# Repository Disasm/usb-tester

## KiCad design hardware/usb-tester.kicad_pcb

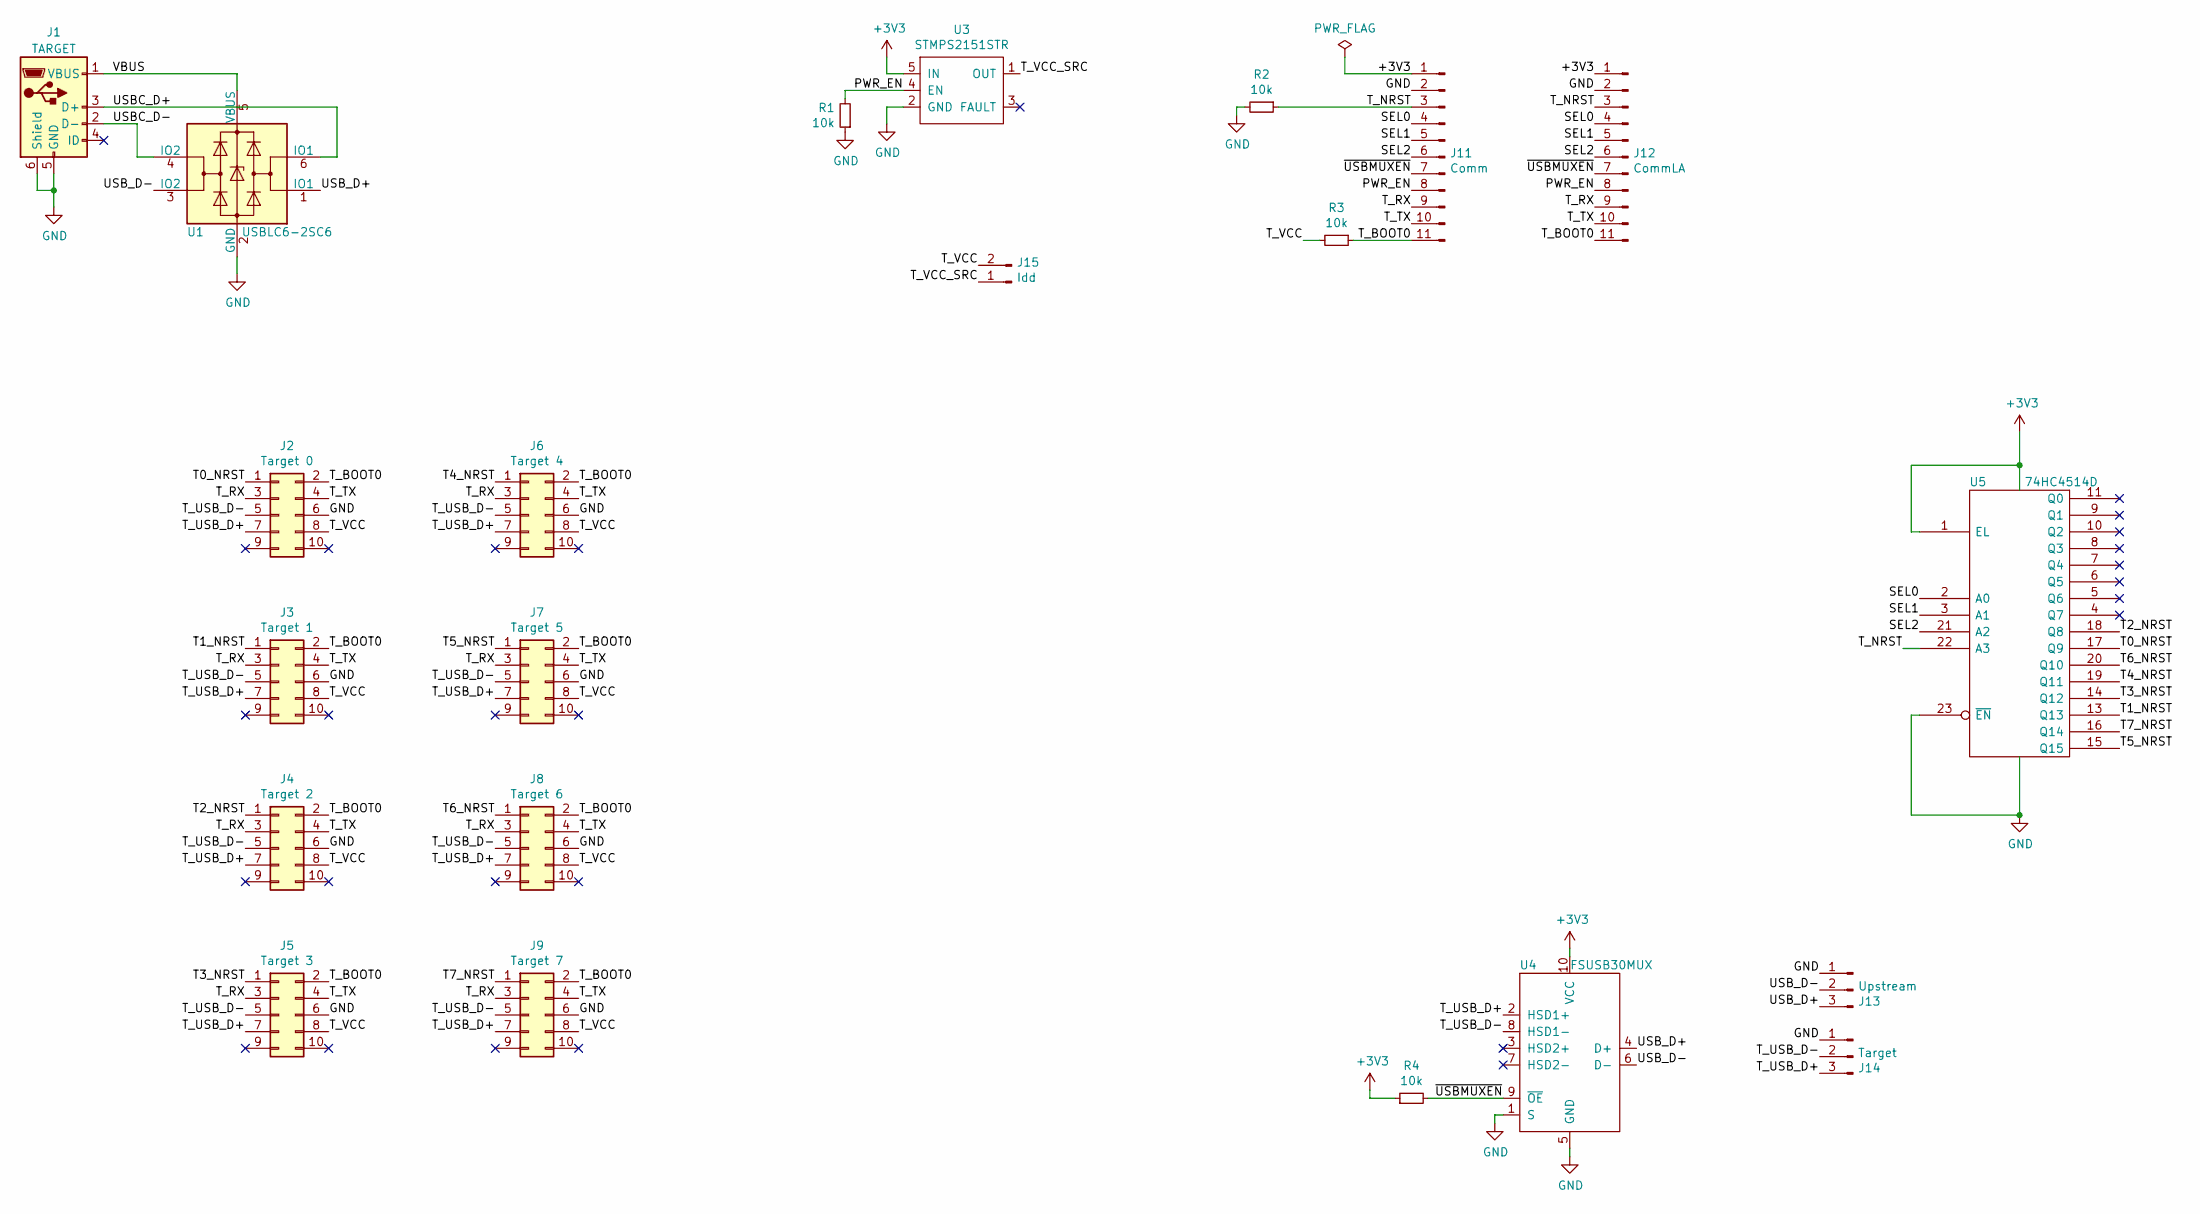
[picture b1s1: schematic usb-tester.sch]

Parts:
J1: TARGET; USB_Micro-B_Molex-105017-0001
J2: Target 0; PinSocket_2x05_P2.54mm_Vertical_Reversed
J3: Target 1; PinSocket_2x05_P2.54mm_Vertical_Reversed
J4: Target 2; PinSocket_2x05_P2.54mm_Vertical_Reversed
J5: Target 3; PinSocket_2x05_P2.54mm_Vertical_Reversed
J6: Target 4; PinSocket_2x05_P2.54mm_Vertical_Reversed
J7: Target 5; PinSocket_2x05_P2.54mm_Vertical_Reversed
J8: Target 6; PinSocket_2x05_P2.54mm_Vertical_Reversed
J9: Target 7; PinSocket_2x05_P2.54mm_Vertical_Reversed
J11: Comm; PinHeader_1x11_P2.54mm_Vertical
J12: CommLA; PinHeader_1x11_P2.54mm_Vertical
J13: Upstream; PinHeader_1x03_P2.54mm_Vertical
J14: Target; PinHeader_1x03_P2.54mm_Vertical
J15: Idd; PinHeader_1x02_P2.54mm_Vertical
R1, R2, R3, R4: 10k; R_1206_3216Metric_Pad1.42x1.75mm_HandSolder
U1: USBLC6-2SC6; SOT-23-6
U3: STMPS2151STR; SOT-23-5
U4: FSUSB30MUX; MSOP-10_3x3mm_P0.5mm
U5: 74HC4514D; SOIC-24W_7.5x15.4mm_P1.27mm

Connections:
+3V3: J11.1, J12.1, R4.1, U3.5 (IN), U4.10 (VCC), U5.1 (EL), U5.24 (Vdd)
/PWR_EN: J11.8, J12.8, R1.2, U3.4 (EN)
/SEL0: J11.4, J12.4, U5.2 (A0)
/SEL1: J11.5, J12.5, U5.3 (A1)
/SEL2: J11.6, J12.6, U5.21 (A2)
/T0_NRST: J2.1, U5.17 (Q9)
/T1_NRST: J3.1, U5.13 (Q13)
/T2_NRST: J4.1, U5.18 (Q8)
/T3_NRST: J5.1, U5.14 (Q12)
/T4_NRST: J6.1, U5.19 (Q11)
/T5_NRST: J7.1, U5.15 (Q15)
/T6_NRST: J8.1, U5.20 (Q10)
/T7_NRST: J9.1, U5.16 (Q14)
/T_BOOT0: J2.2, J3.2, J4.2, J5.2, J6.2, J7.2, J8.2, J9.2, J11.11, J12.11, R3.1
/T_NRST: J11.3, J12.3, R2.1, U5.22 (A3)
/T_RX: J2.3, J3.3, J4.3, J5.3, J6.3, J7.3, J8.3, J9.3, J11.9, J12.9
/T_TX: J2.4, J3.4, J4.4, J5.4, J6.4, J7.4, J8.4, J9.4, J11.10, J12.10
/T_USB_D+: J2.7, J3.7, J4.7, J5.7, J6.7, J7.7, J8.7, J9.7, J14.3, U4.2 (HSD1+)
/T_USB_D-: J2.5, J3.5, J4.5, J5.5, J6.5, J7.5, J8.5, J9.5, J14.2, U4.8 (HSD1-)
/T_VCC: J2.8, J3.8, J4.8, J5.8, J6.8, J7.8, J8.8, J9.8, J15.2, R3.2
/T_VCC_SRC: J15.1, U3.1 (OUT)
/USBC_D+: J1.3 (D+), U1.6 (IO1)
/USBC_D-: J1.2 (D-), U1.4 (IO2)
/USB_D+: J13.3, U1.1 (IO1), U4.4 (D+)
/USB_D-: J13.2, U1.3 (IO2), U4.6 (D-)
/VBUS: J1.1 (VBUS), U1.5 (VBUS)
/~USBMUXEN: J11.7, J12.7, R4.2, U4.9 (~OE)
GND: J1.5 (GND), J1.6 (Shield), J2.6, J3.6, J4.6, J5.6, J6.6, J7.6, J8.6, J9.6, J11.2, J12.2, J13.1, J14.1, R1.1, R2.2, U1.2 (GND), U3.2 (GND), U4.1 (S), U4.5 (GND), U5.12 (Vss), U5.23 (~EN)

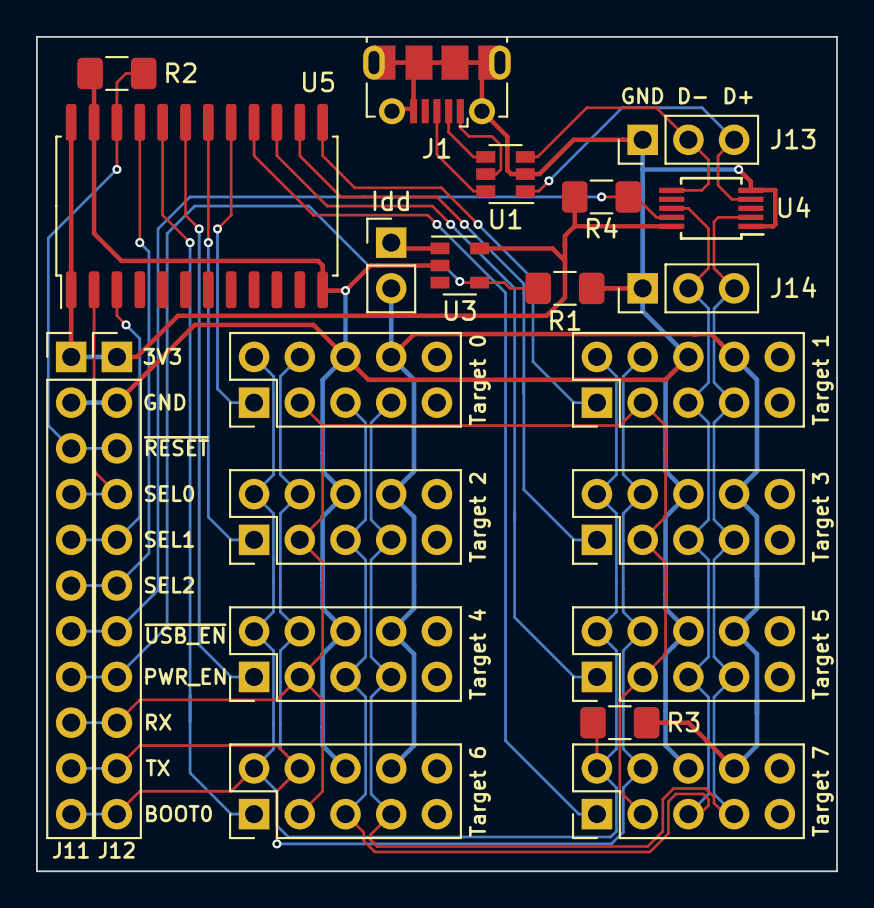
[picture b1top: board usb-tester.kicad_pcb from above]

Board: 2 copper layers, 44.5 x 46.4 mm, 22 parts (0 on the bottom side), 28 nets.

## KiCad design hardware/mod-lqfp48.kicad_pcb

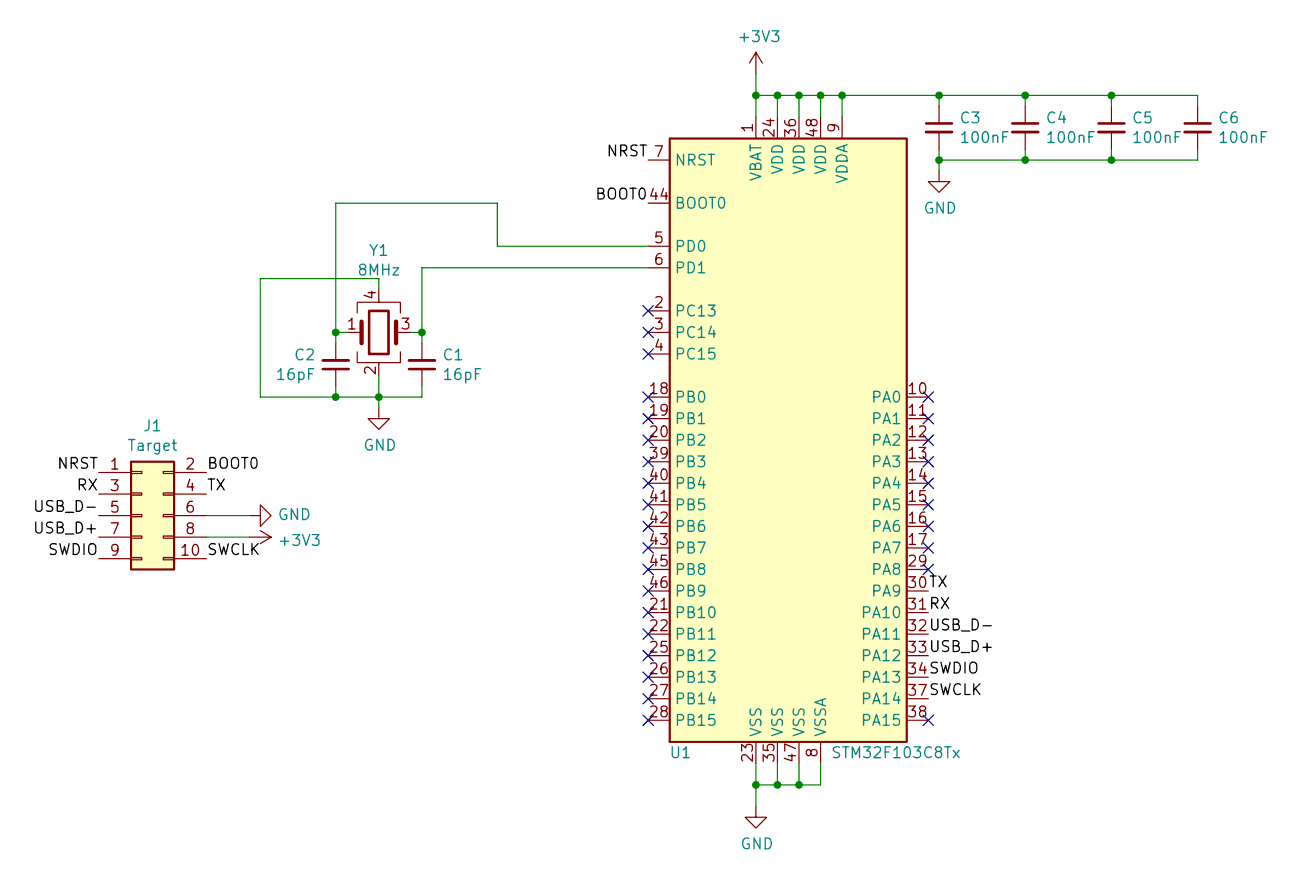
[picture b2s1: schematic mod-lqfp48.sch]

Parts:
C1, C2: 16pF; C_0805_2012Metric_Pad1.15x1.40mm_HandSolder
C3, C4, C5, C6: 100nF; C_0805_2012Metric_Pad1.15x1.40mm_HandSolder
J1: Target; BH-10-Edge
U1: STM32F103C8Tx; LQFP-48_7x7mm_P0.5mm
Y1: 8MHz; Crystal_SMD_5032-4Pin_5.0x3.2mm

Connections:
+3V3: C3.1, C4.1, C5.1, C6.1, J1.8, U1.1 (VBAT), U1.9 (VDDA), U1.24 (VDD), U1.36 (VDD), U1.48 (VDD)
/BOOT0: J1.2, U1.44 (BOOT0)
/NRST: J1.1, U1.7 (NRST)
/RX: J1.3, U1.31 (PA10)
/SWCLK: J1.10, U1.37 (PA14)
/SWDIO: J1.9, U1.34 (PA13)
/TX: J1.4, U1.30 (PA9)
/USB_D+: J1.7, U1.33 (PA12)
/USB_D-: J1.5, U1.32 (PA11)
GND: C1.1, C2.1, C3.2, C4.2, C5.2, C6.2, J1.6, U1.8 (VSSA), U1.23 (VSS), U1.35 (VSS), U1.47 (VSS), Y1.2, Y1.4
unnamed: C1.2, U1.6 (PD1), Y1.3
unnamed: C2.2, U1.5 (PD0), Y1.1

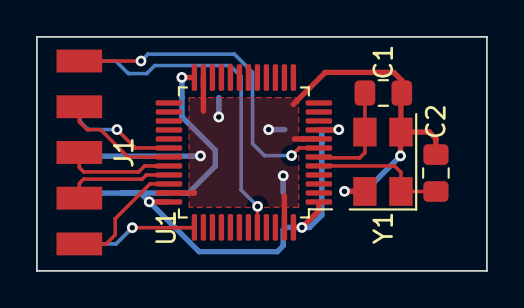
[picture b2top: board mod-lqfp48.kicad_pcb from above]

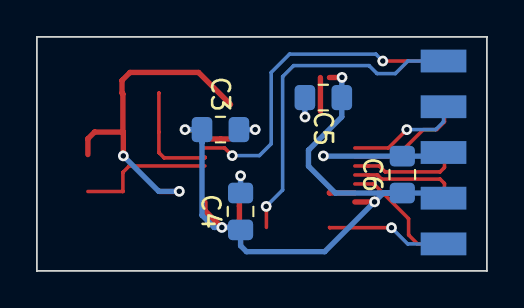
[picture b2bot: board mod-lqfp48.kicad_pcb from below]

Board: 2 copper layers, 25.0 x 13.0 mm, 9 parts (4 on the bottom side), 12 nets.

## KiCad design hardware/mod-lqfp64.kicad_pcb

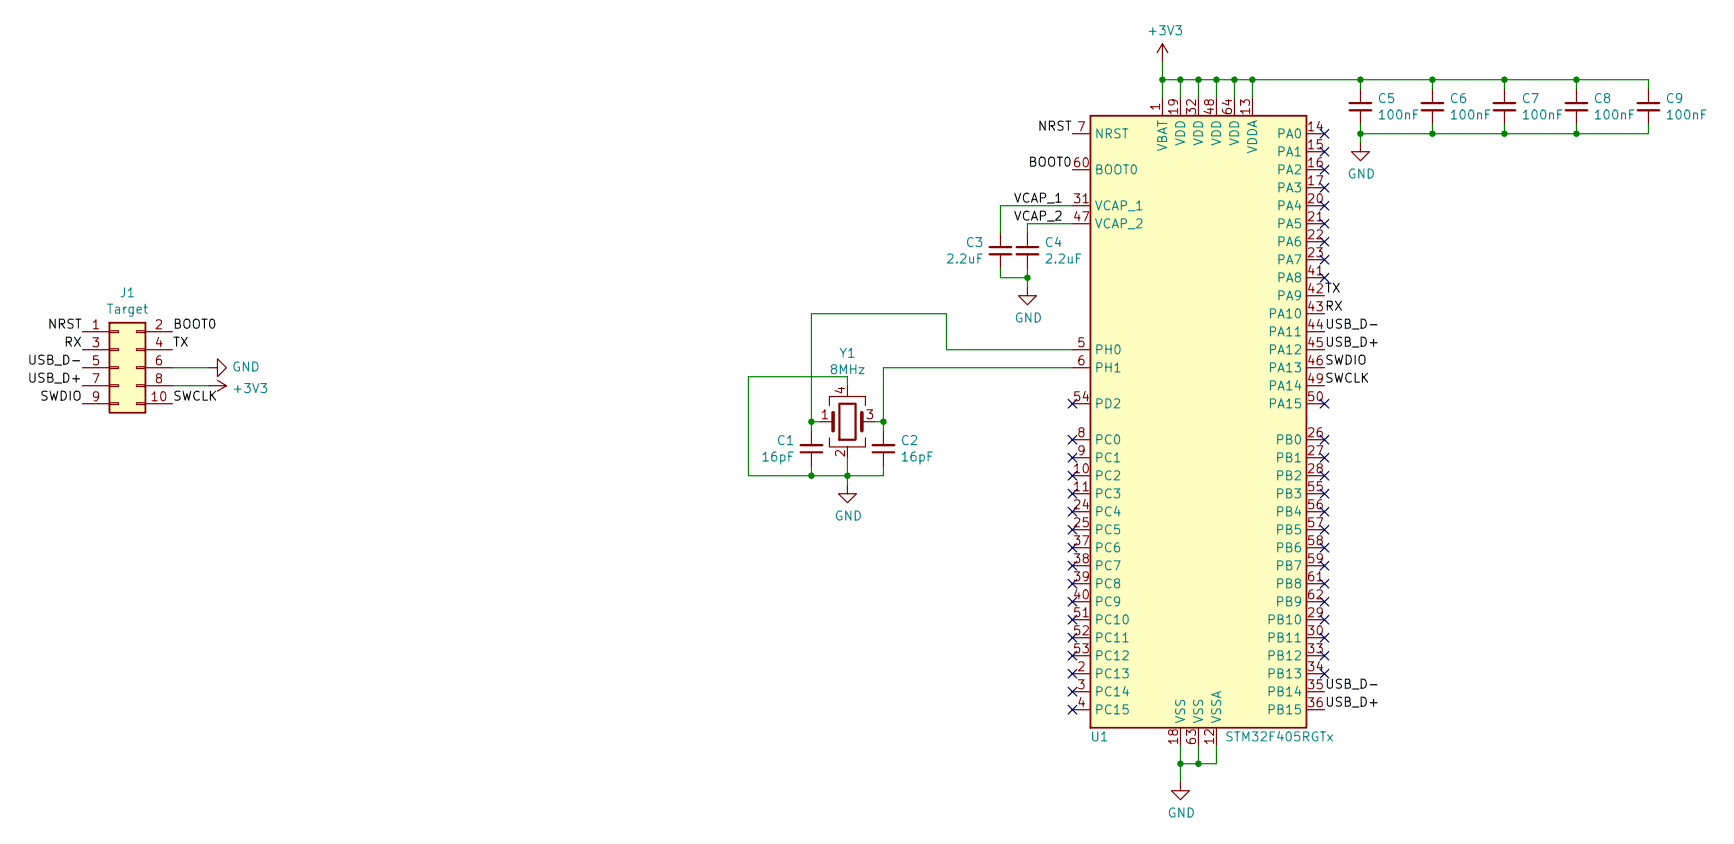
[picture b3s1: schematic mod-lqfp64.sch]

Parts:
C1, C2: 16pF; C_0805_2012Metric_Pad1.15x1.40mm_HandSolder
C3, C4: 2.2uF; C_0805_2012Metric_Pad1.15x1.40mm_HandSolder
C5, C6, C7, C8, C9: 100nF; C_0805_2012Metric_Pad1.15x1.40mm_HandSolder
J1: Target; BH-10-Edge
U1: STM32F405RGTx; LQFP-64_10x10mm_P0.5mm
Y1: 8MHz; Crystal_SMD_5032-4Pin_5.0x3.2mm

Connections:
+3V3: C5.1, C6.1, C7.1, C8.1, C9.1, J1.8, U1.1 (VBAT), U1.13 (VDDA), U1.19 (VDD), U1.32 (VDD), U1.48 (VDD), U1.64 (VDD)
/BOOT0: J1.2, U1.60 (BOOT0)
/NRST: J1.1, U1.7 (NRST)
/RX: J1.3, U1.43 (PA10)
/SWCLK: J1.10, U1.49 (PA14)
/SWDIO: J1.9, U1.46 (PA13)
/TX: J1.4, U1.42 (PA9)
/USB_D+: J1.7, U1.36 (PB15), U1.45 (PA12)
/USB_D-: J1.5, U1.35 (PB14), U1.44 (PA11)
/VCAP_1: C3.1, U1.31 (VCAP_1)
/VCAP_2: C4.1, U1.47 (VCAP_2)
GND: C1.1, C2.1, C3.2, C4.2, C5.2, C6.2, C7.2, C8.2, C9.2, J1.6, U1.12 (VSSA), U1.18 (VSS), U1.63 (VSS), Y1.2, Y1.4
unnamed: C1.2, U1.5 (PH0), Y1.1
unnamed: C2.2, U1.6 (PH1), Y1.3

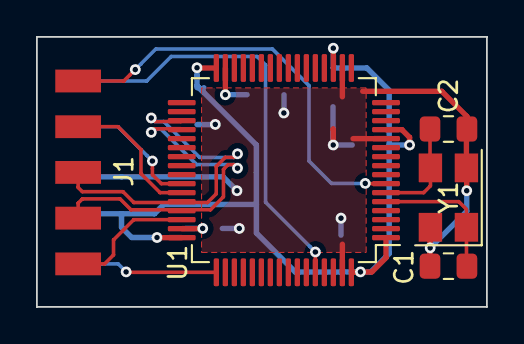
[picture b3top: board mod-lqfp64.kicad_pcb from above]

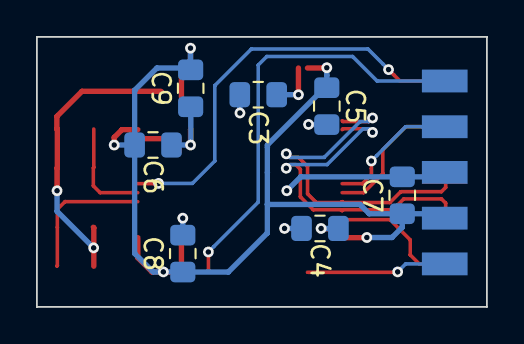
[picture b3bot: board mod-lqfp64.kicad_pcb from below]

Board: 2 copper layers, 25.0 x 15.0 mm, 12 parts (7 on the bottom side), 14 nets.

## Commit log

2020-02-06 WIP hardware
2020-02-06 Move symbols to 'ic' library
2020-02-06 Muxes
2020-02-11 Base board
2020-02-11 mod-lqfp48 board WIP
2020-02-12 mod-lqfp48 board schematic finished
2020-02-19 mod-lqfp48 is finally routed
2020-02-19 mod-lqfp64 schematic
2020-02-19 mod-lqfp64 board layout
2020-02-19 Rotate references
2020-02-20 Updated connectors and labels on the main board
2020-02-20 Main board schematic
2020-02-20 WIP main board
2020-02-20 Use separate USBSEL signal for USB switches
2020-02-22 WIP main board layout
2020-02-24 Use the same net for FS and HS USB
2020-02-24 Update mod-lqfp64 board layout
2020-02-24 Fix DRC warnings in mod-lqfp48
2020-02-24 Move labels
2020-02-24 Use Rezonit solder mask parameters
2020-02-24 Align boards to the 1mm grid
2020-02-24 Resize the mod-lqfp48 board
2020-03-03 Add gerber files for mod-lqfp48 and mod-lqfp64
2020-03-04 Add firmware and pc client
2020-03-05 Use even parity for communicating with a bootloader
2020-03-05 Read from USB regardless of USB poll() events
2020-03-05 Open serial port component of the usb switch
2020-03-05 Cleanup
2020-04-06 Simplify schematics, add WIP layout
2020-05-17 Finalize shematics and layout
2020-05-17 Fix ERC errors
2020-05-17 Re-import netlist
2020-05-17 Ignore overlapping courtyards
2020-05-17 Update design rules
2020-05-18 Update KiCad libraries
2020-05-18 Use reversed footprint instead of a standard one
2020-05-18 Update layout
2020-05-18 Add labels
2020-05-18 Tune silkscreen params a little bit
2020-05-18 Add gerbers for the usb-tester board
2020-05-22 Return serial port path instead of serial object
2020-05-22 Add support for the bootloader protocol
2020-05-24 Add support for 1-bit selector
2020-05-24 Perform poweroff cycle before talking to a bootloader
2020-05-24 Decode device id
2020-05-24 Check for supported commands
2020-05-24 Use eprintln for errors
2020-05-24 Use safe selection after startup
2020-05-24 Do not keep NRST and BOOT0 lines high during powerdown
